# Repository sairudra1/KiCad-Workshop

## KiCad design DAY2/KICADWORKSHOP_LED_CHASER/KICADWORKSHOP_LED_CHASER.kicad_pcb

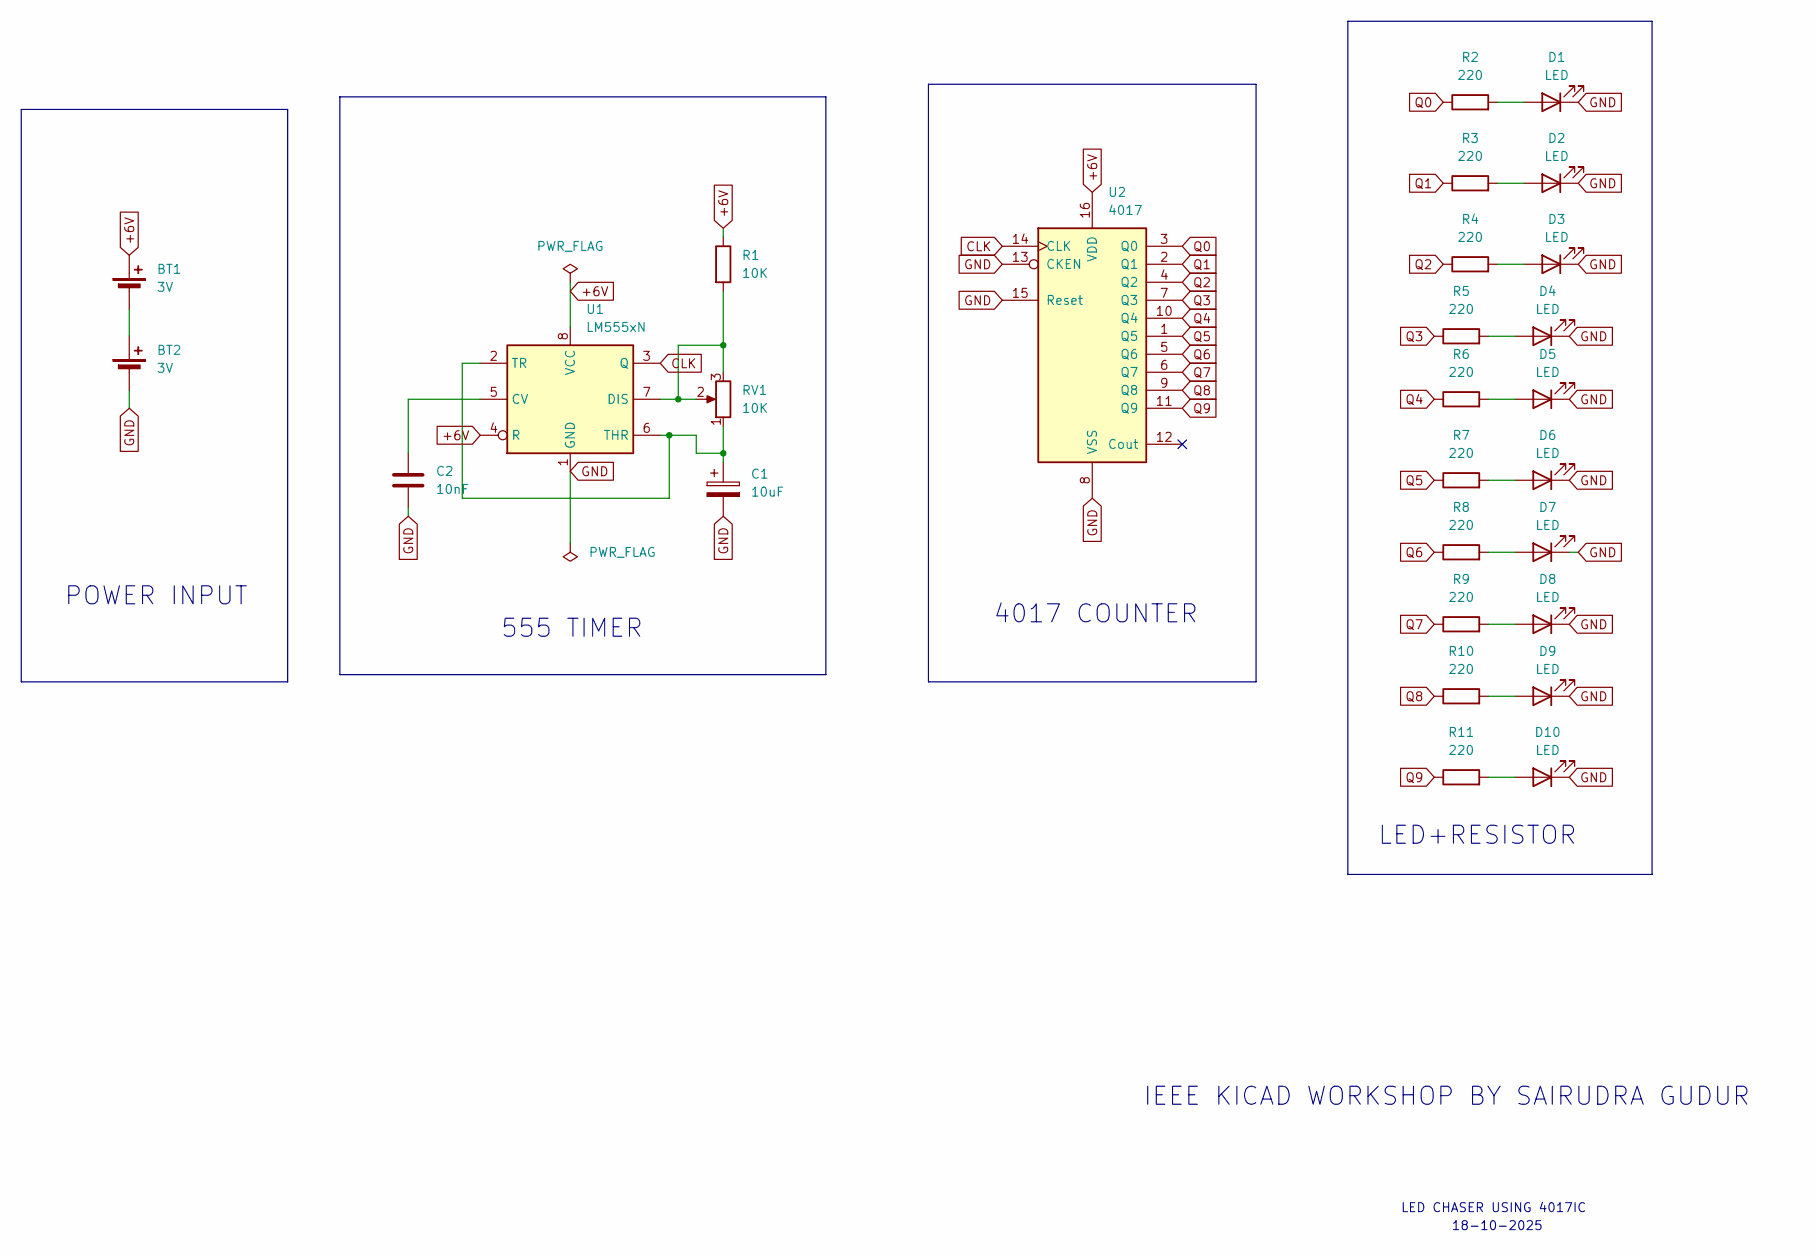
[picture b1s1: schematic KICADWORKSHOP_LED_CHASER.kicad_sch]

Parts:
BT1, BT2: 3V; BatteryHolder_MYOUNG_BS-07-A1BJ001_CR2032
C1: 10uF; CP_Radial_D4.0mm_P2.00mm
C2: 10nF; C_0805_2012Metric
D1, D2, D3, D4, D5, D6, D7, D8, D9: LED; LED_D3.0mm
D10: LED; LED_0805_2012Metric_Pad1.15x1.40mm_HandSolder
R1: 10K; R_Axial_DIN0207_L6.3mm_D2.5mm_P10.16mm_Horizontal
R2, R3, R4, R5, R6, R7, R8, R9, R10: 220; R_Axial_DIN0207_L6.3mm_D2.5mm_P10.16mm_Horizontal
R11: 220; R_0805_2012Metric
RV1: 10K; Potentiometer_Bourns_3386P_Vertical
U1: LM555xN; DIP-8_W7.62mm
U2: 4017; DIP-16_W7.62mm

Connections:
+6V: BT1.1 (+), R1.1, U1.4 (R), U1.8 (VCC), U2.16 (VDD)
CLK: U1.3 (Q), U2.14 (CLK)
GND: BT2.2 (-), C1.2, C2.2, D1.1 (K), D2.1 (K), D3.1 (K), D4.1 (K), D5.1 (K), D6.1 (K), D7.1 (K), D8.1 (K), D9.1 (K), D10.1 (K), U1.1 (GND), U2.8 (VSS), U2.13 (CKEN), U2.15 (Reset)
unnamed: BT1.2 (-), BT2.1 (+)
unnamed: D1.2 (A), R2.2
unnamed: D2.2 (A), R3.2
unnamed: D3.2 (A), R4.2
unnamed: D4.2 (A), R5.2
unnamed: D5.2 (A), R6.2
unnamed: D6.2 (A), R7.2
unnamed: D7.2 (A), R8.2
unnamed: D8.2 (A), R9.2
unnamed: D9.2 (A), R10.2
unnamed: D10.2 (A), R11.2
unnamed: C2.1, U1.5 (CV)
unnamed: R1.2, RV1.2, RV1.3, U1.7 (DIS)
unnamed: C1.1, RV1.1, U1.2 (TR), U1.6 (THR)
Q0: R2.1, U2.3 (Q0)
Q1: R3.1, U2.2 (Q1)
Q2: R4.1, U2.4 (Q2)
Q3: R5.1, U2.7 (Q3)
Q4: R6.1, U2.10 (Q4)
Q5: R7.1, U2.1 (Q5)
Q6: R8.1, U2.5 (Q6)
Q7: R9.1, U2.6 (Q7)
Q8: R10.1, U2.9 (Q8)
Q9: R11.1, U2.11 (Q9)

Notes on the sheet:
POWER INPUT
18-10-2025
LED+RESISTOR
IEEE KICAD WORKSHOP BY SAIRUDRA GUDUR
LED CHASER USING 4017IC
555 TIMER
4017 COUNTER

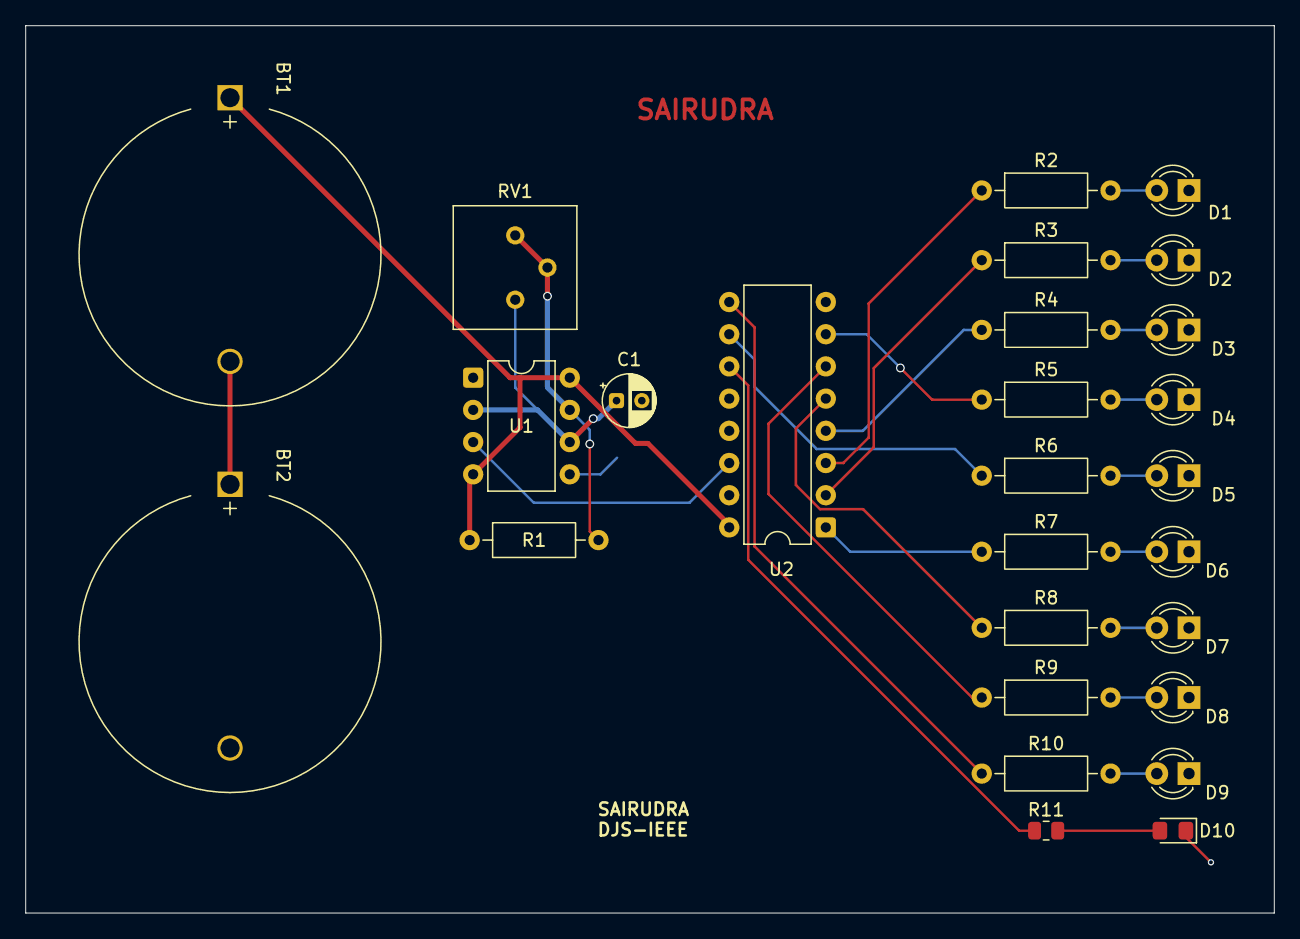
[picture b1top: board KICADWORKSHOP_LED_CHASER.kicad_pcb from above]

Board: 2 copper layers, 98.5 x 70.0 mm, 28 parts (1 on the bottom side), 27 nets.

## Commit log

2025-10-18 Day1 progress
2025-10-19 Day2
